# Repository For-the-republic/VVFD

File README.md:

# VVFD
 Variable VFD display driver for any electromagnet based VFD.
 made by Sam Ramsay and Luke Quigley
# PREREQUISTES

## It must have a leakage current
VFDs are funny little things, as even though the have vacumn in the name, most are not a pure vacumn. instead they have a small amount of gas in them. this is only true for larger ( or more delacite ones), and is the main operation which we are measuring to find the anode connections.

## how to tell if you have a leakage current
the best way to tell if it has a leakage current is by the datasheet. if it has **both** a current draw on the segment and grid, you have a leakage. 

the next best way to tell is by the size of the VFD. smaller VFDs tend to be pure vacumns, and dont have a leakage current. if it is a larger (or older) VFD like those found in audio amplifiers, car radios ect, it most likely has a leakage current.

the third and final way to tell is to manually check. if there is a leakage current, **there will be a small current increase when a valid grid/segment combination is found**. this is by far the best way to tell, however can be quite finnicky and so we reccomend the other ways first.

# how this works
 it detects a leakage in current across different pins, and will make an anode connection table accordingly.
  this is still in development so it might take a while to get up and running.

# setup process and PCB information
the PCB is designed to be cascaded for extra modules to fit your VFD size. each module can have 32 pins, and only requires the cascade/vfd driver components. the original board will still need the drivers, but no other ones will.
## setup information
the two values you will need to change  are:
- PINCOUNT
PINCOUNT is the number of shift registers used, starting from the main module and cascading to the right. we need to know this so we can properly push the right bits.

compile this code to your arduino, and have it plugged in to accept serial out. the arduino will print your matrix to the serial out, so its kinda important.

to set the base conditions, the the arduino runs it will go into setup mode for one minute. this gives you time to ajust the variable resistors, and make sure everything is working. **DO NOT CHANGE THE RESISTORS AFTER ONE MINUTE**, or else the ammeters wont have a base value to test off of.

once this mode is done, just leave it. 
## when it has finished
once it has completed making the pinout table, it will cycle through every valid combonation and send a matrix to the serial out of the arduino.

## a note about pinouts
**if in doubt, use the pinout schematic/PCB provided**
- the AC generator pins must be both PWN pins
- the ammeter pins must be analouge
- all other pins should combos should be fine

[video of it working](https://youtu.be/ehEdY2yYjXk)

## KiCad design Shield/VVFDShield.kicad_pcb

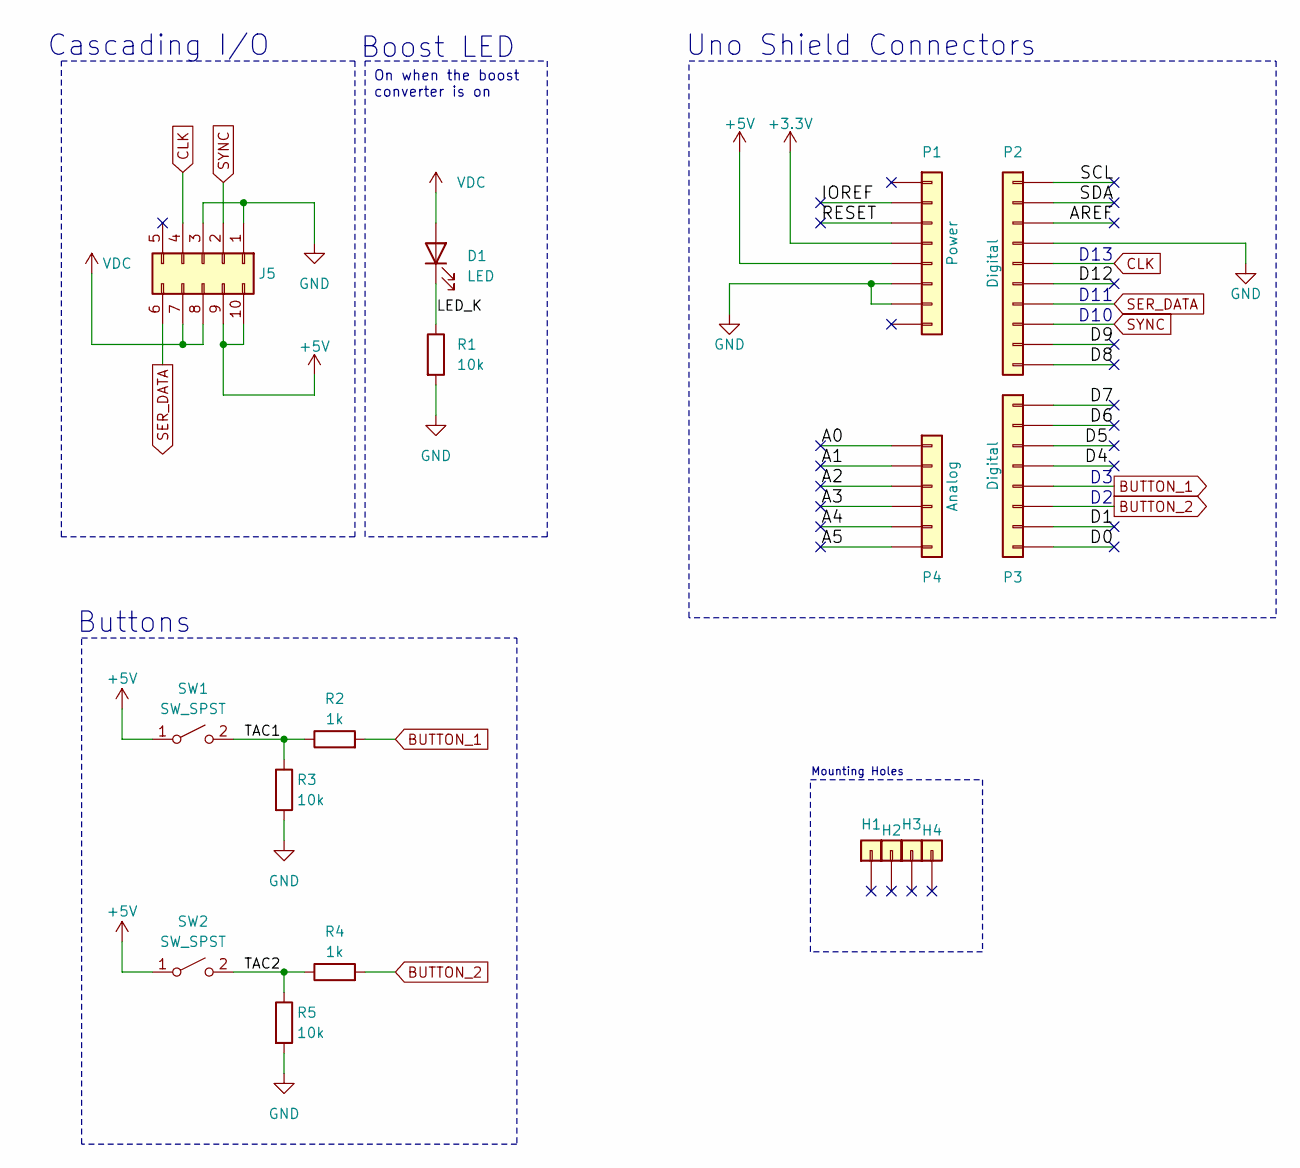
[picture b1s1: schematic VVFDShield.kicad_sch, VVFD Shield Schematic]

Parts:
D1: LED; LED_D5.0mm
H1, H2, H3, H4: CONN_01X01; Mounting_Hole
J5: Conn_02x05_Counter_Clockwise; IDC-Header_2x05_P2.54mm_Vertical; Digikey Part No UC
P1: Power; Socket_Strip_Arduino_1x08
P2: Digital; Socket_Strip_Arduino_1x10
P3: Digital; Socket_Strip_Arduino_1x08
P4: Analog; Socket_Strip_Arduino_1x06
R1, R3, R5: 10k; R_Axial_DIN0207_L6.3mm_D2.5mm_P7.62mm_Horizontal
R2, R4: 1k; R_Axial_DIN0207_L6.3mm_D2.5mm_P7.62mm_Horizontal
SW1, SW2: SW_SPST; SW_PUSH_6mm

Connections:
+3.3V: P1.4
+5V: J5.9, J5.10, P1.5, SW1.1 (A), SW2.1 (A)
/A0: P4.1
/A1: P4.2
/A2: P4.3
/A3: P4.4
/A4: P4.5
/A5: P4.6
/AREF: P2.3
/D0: P3.8
/D1: P3.7
/D4: P3.4
/D5: P3.3
/D6: P3.2
/D7: P3.1
/D8: P2.10
/D9: P2.9
/D12: P2.6
/IOREF: P1.2
/LED_K: D1.1 (K), R1.1
/RESET: P1.3
/SCL: P2.1
/SDA: P2.2
/TAC1: R2.1, R3.1, SW1.2 (B)
/TAC2: R4.1, R5.1, SW2.2 (B)
BUTTON_1: P3.5, R2.2
BUTTON_2: P3.6, R4.2
CLK: J5.4, P2.5
GND: J5.1, J5.3, P1.6, P1.7, P2.4, R1.2, R3.2, R5.2
SER_DATA: J5.6, P2.7
SYNC: J5.2, P2.8
VDC: D1.2 (A), J5.7, J5.8

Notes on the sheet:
Cascading I/O
Uno Shield Connectors
Buttons
Boost LED
D13
Mounting Holes
D10
D11
On when the boost converter is on

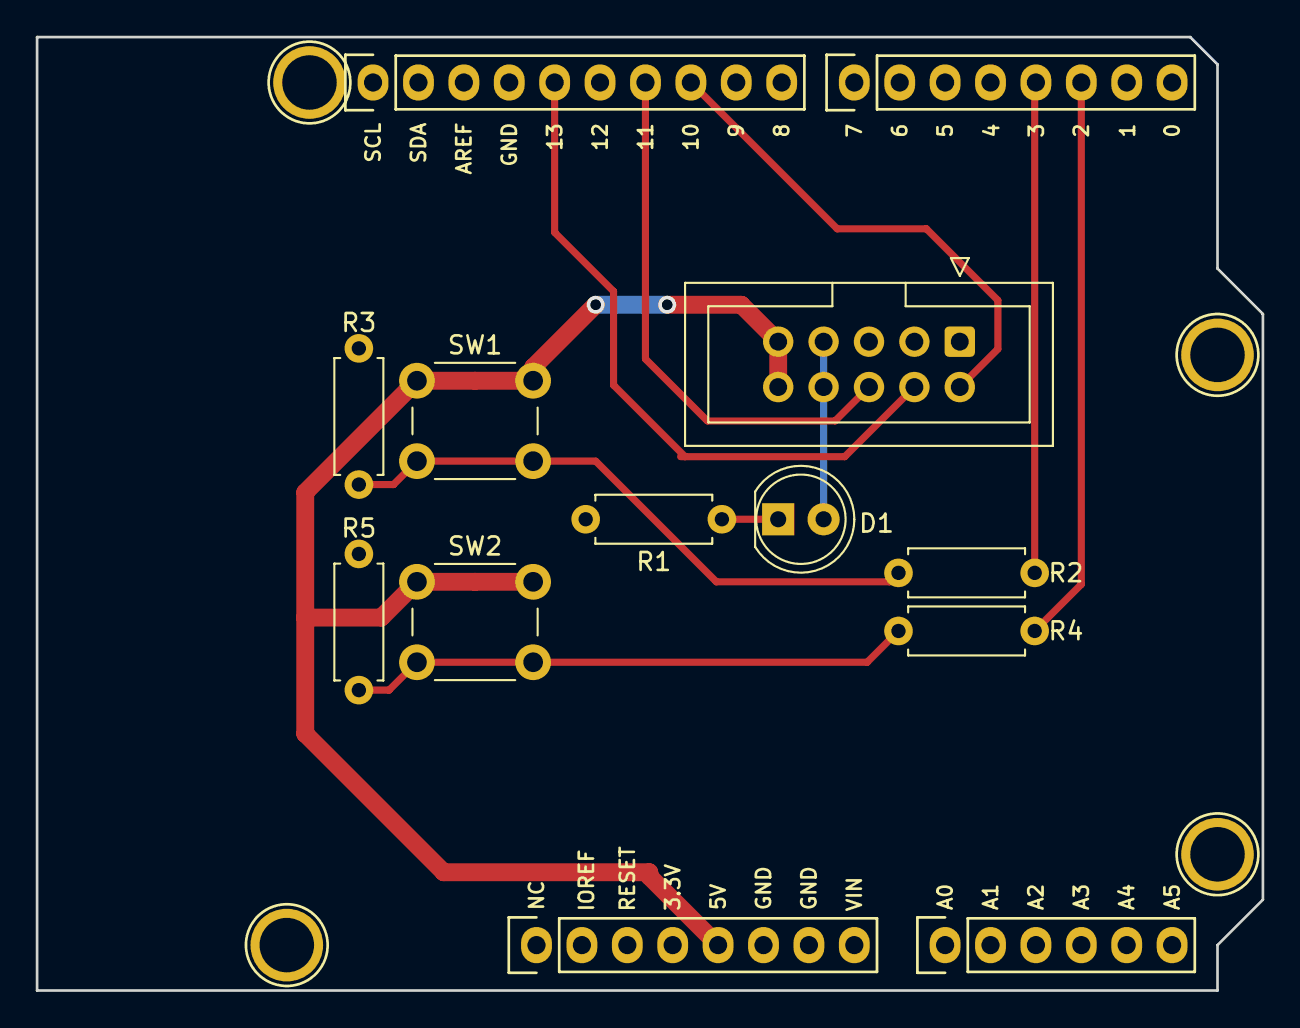
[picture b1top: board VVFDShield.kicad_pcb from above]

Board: 2 copper layers, 68.6 x 53.3 mm, 17 parts (0 on the bottom side), 11 nets.

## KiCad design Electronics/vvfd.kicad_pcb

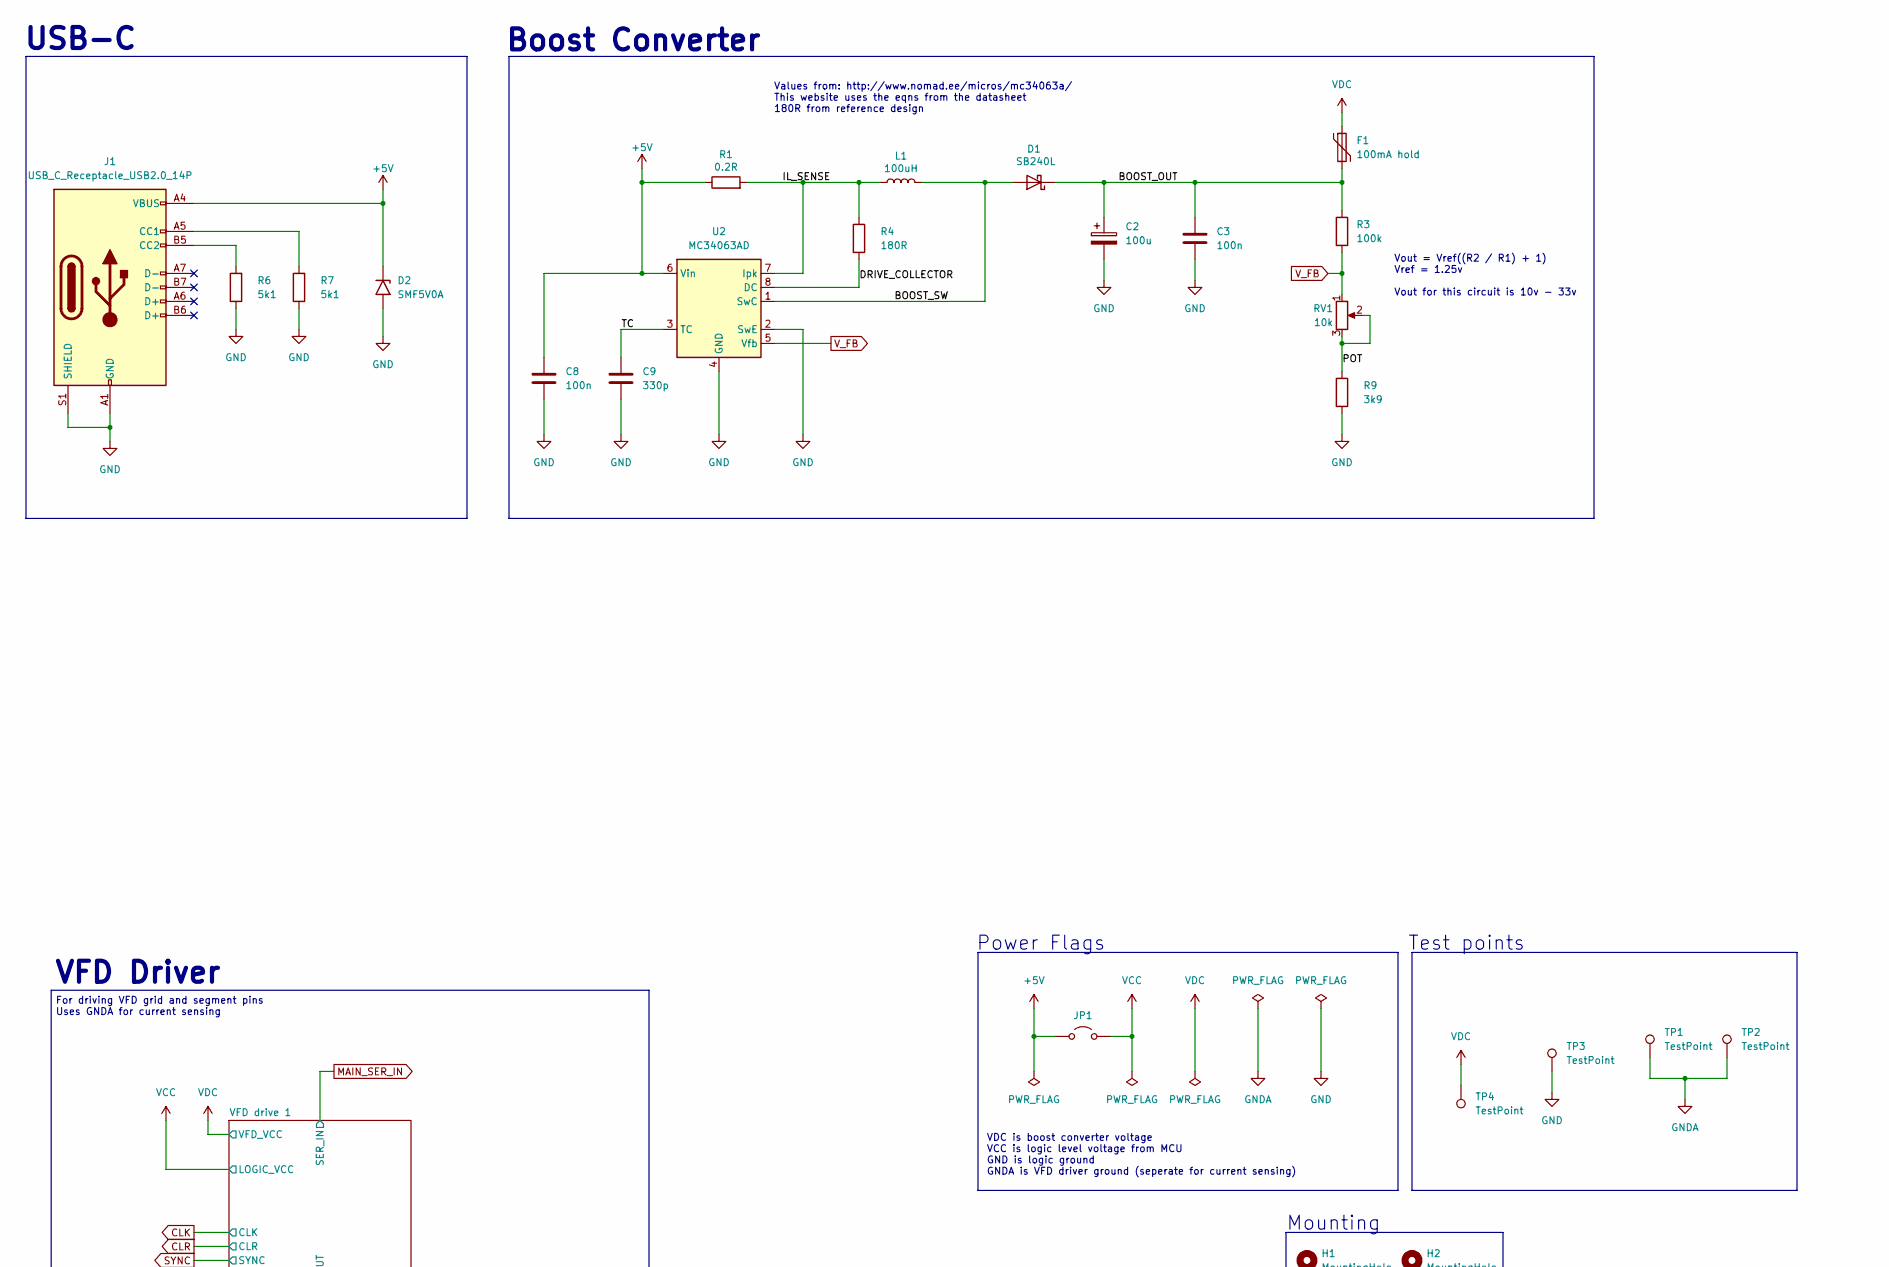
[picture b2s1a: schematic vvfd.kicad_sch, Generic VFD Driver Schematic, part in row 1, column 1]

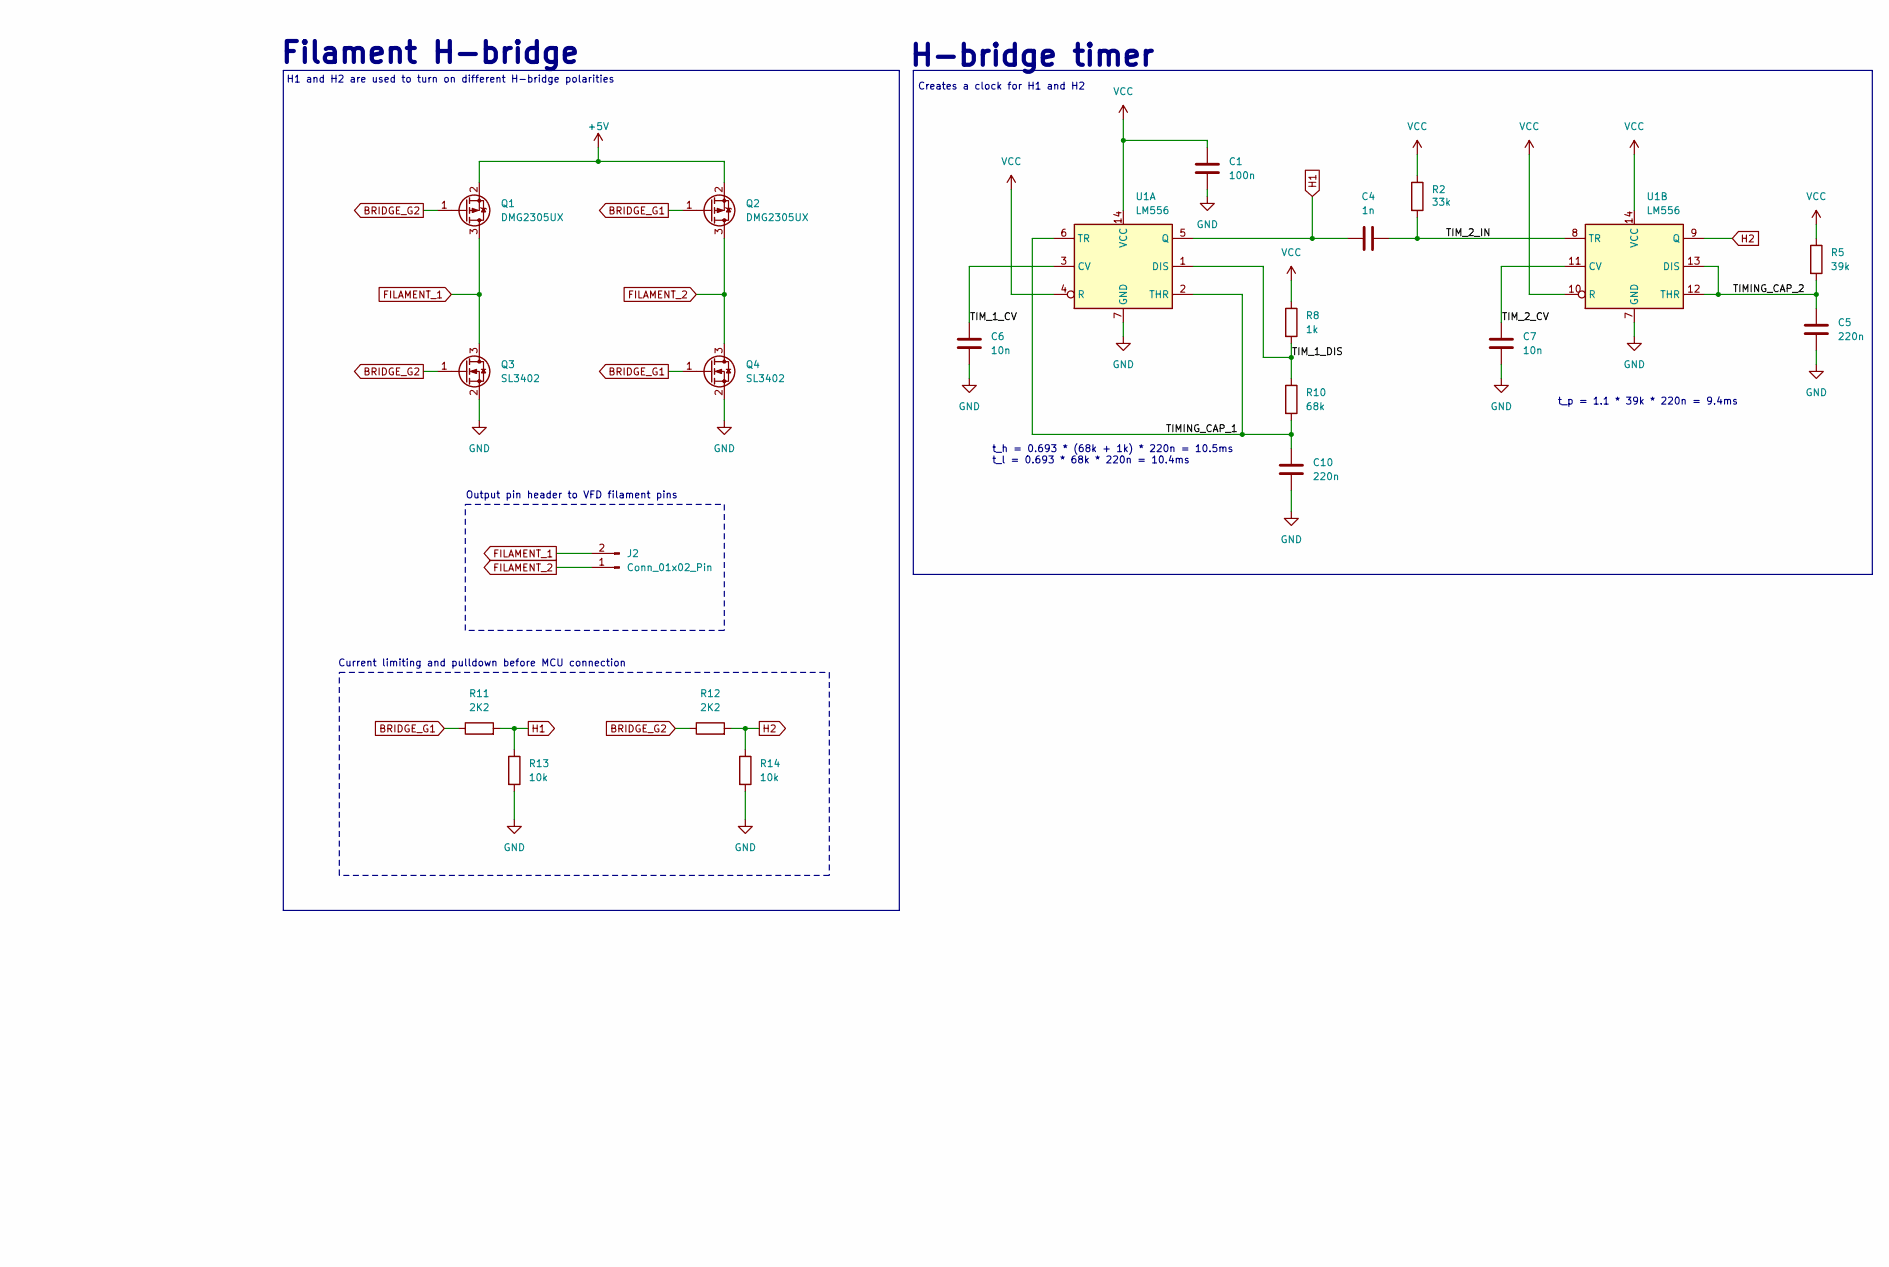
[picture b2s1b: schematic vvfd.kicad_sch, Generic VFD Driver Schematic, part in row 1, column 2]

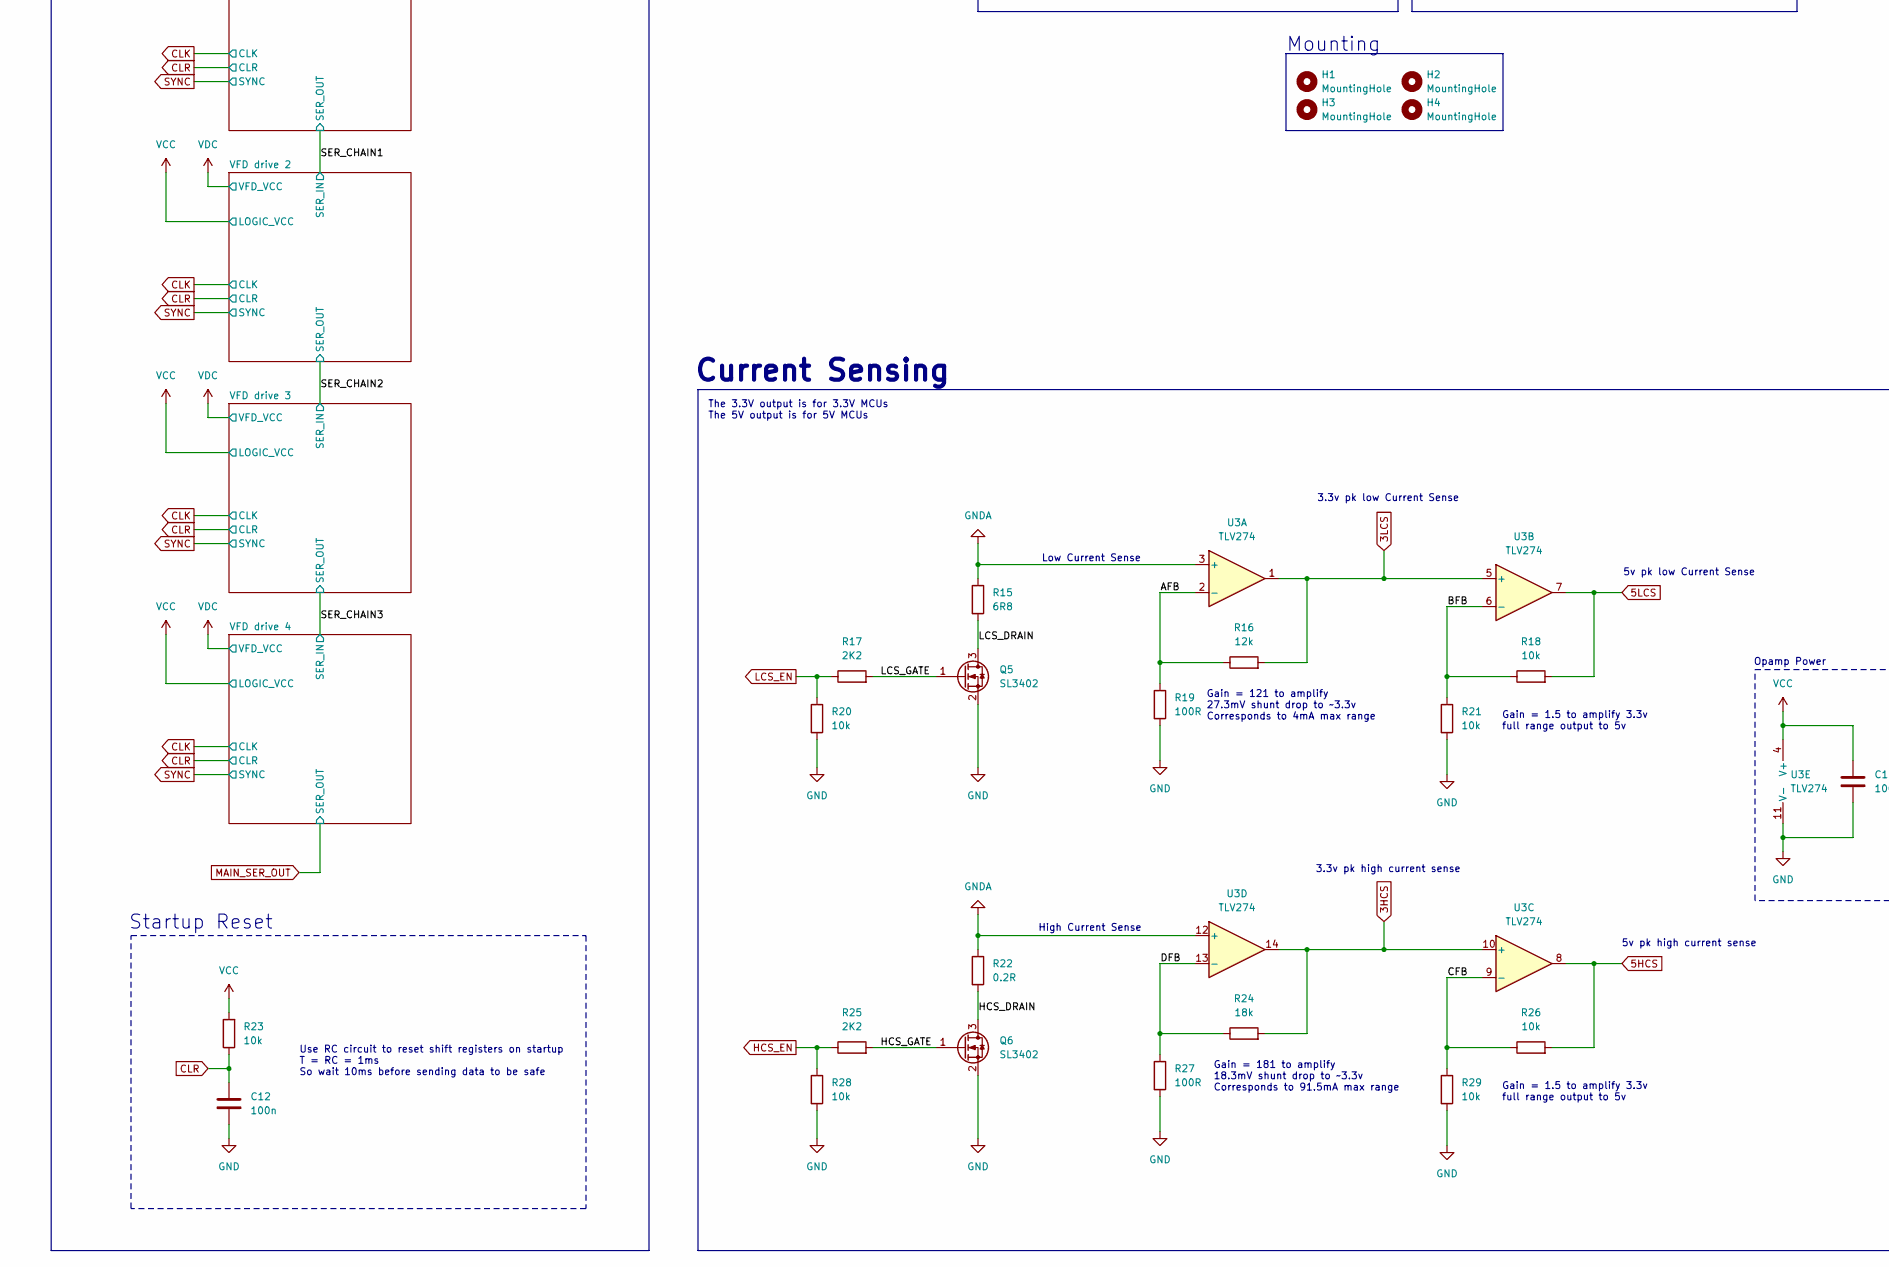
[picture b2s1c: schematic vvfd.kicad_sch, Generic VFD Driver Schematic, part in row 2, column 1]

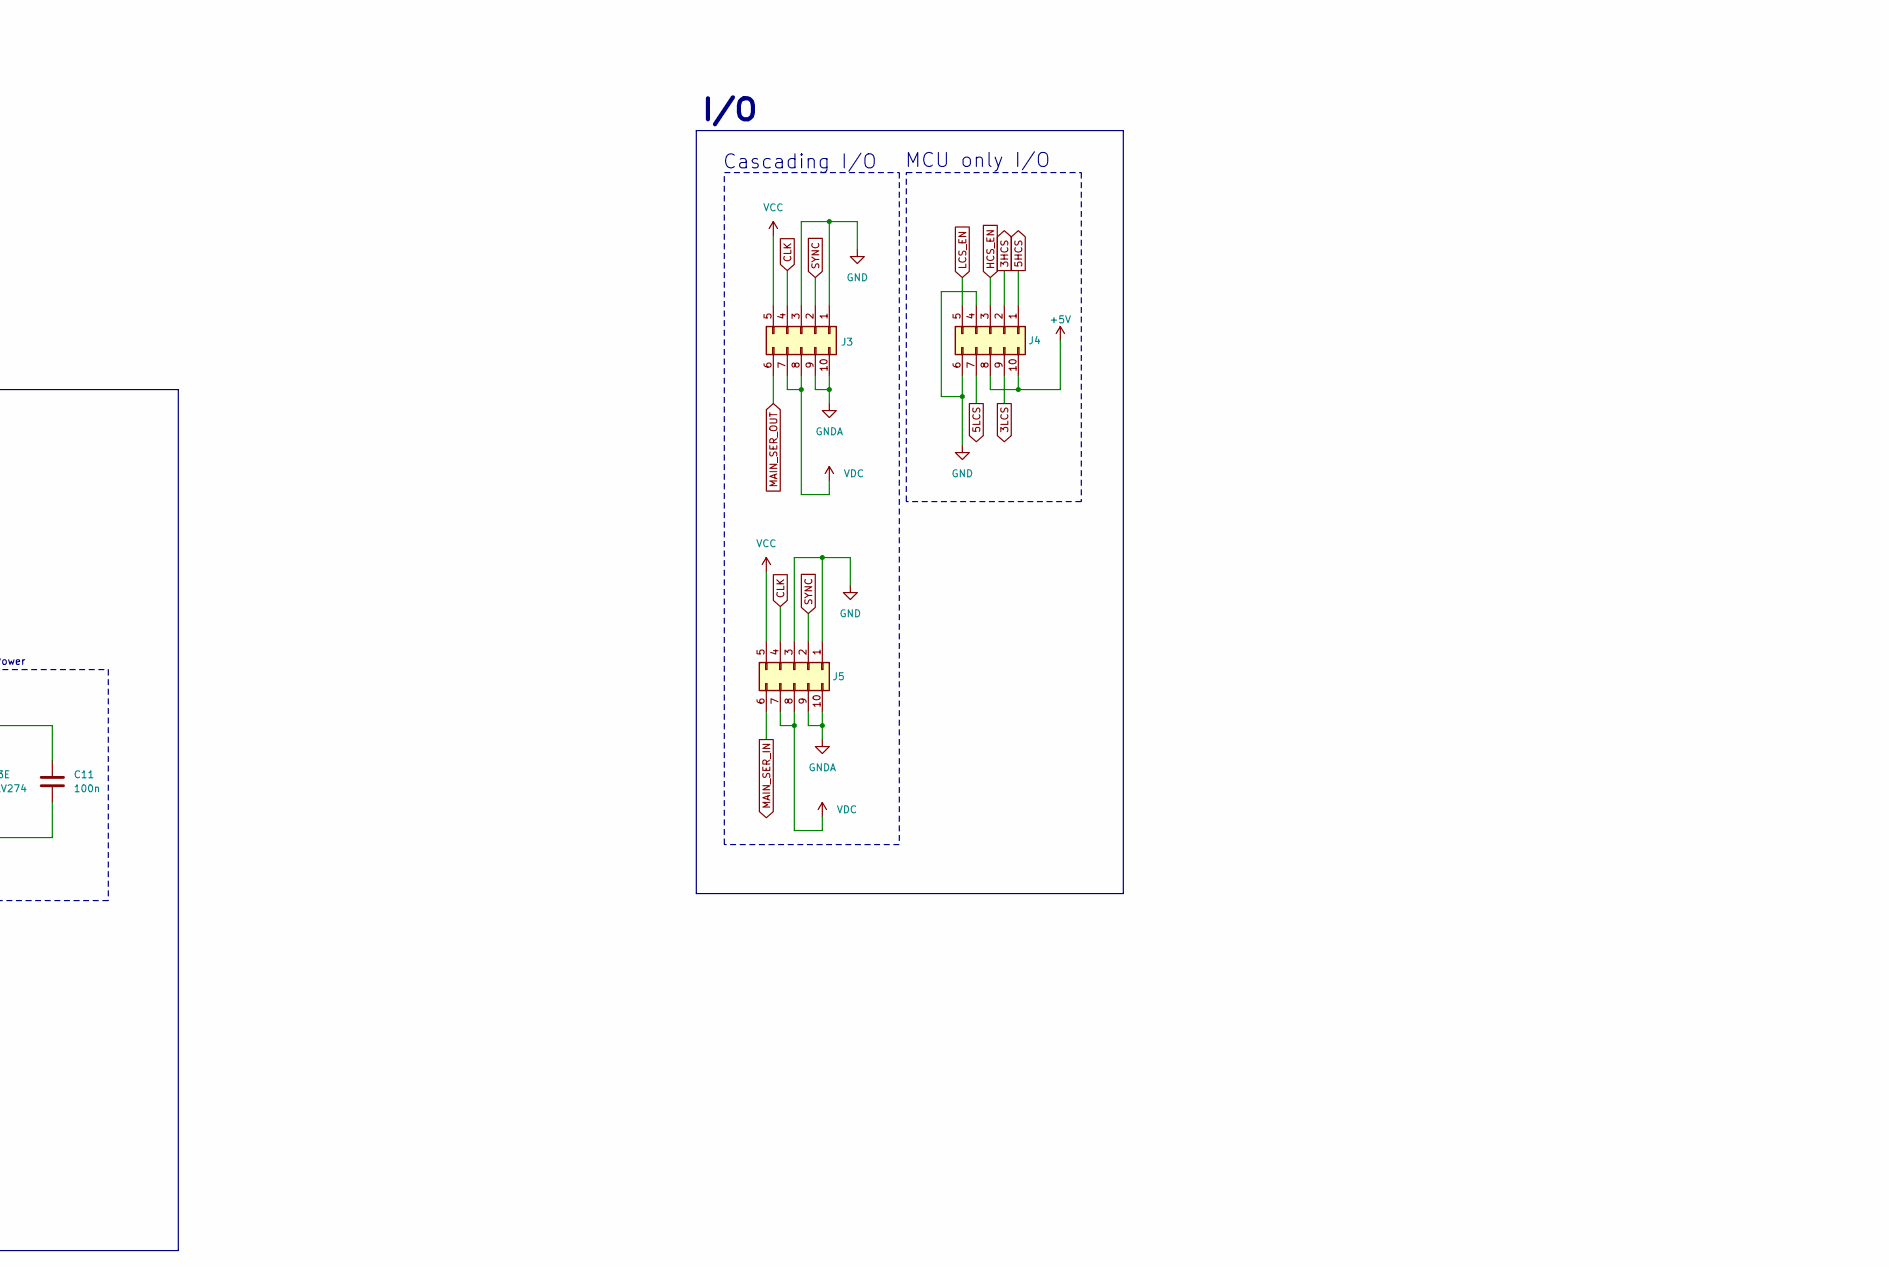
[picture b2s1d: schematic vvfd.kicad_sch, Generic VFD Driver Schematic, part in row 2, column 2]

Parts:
C1, C3, C8, C11, C12: 100n; C_Disc_D5.1mm_W3.2mm_P5.00mm; Digikey Part No UC
C2: 100u; C_Radial_D8.0mm_H11.5mm_P3.50mm; Manufacturer Part No 860080674009; Digikey Part No 732-9051-1-ND
C4: 1n; C_Disc_D5.1mm_W3.2mm_P5.00mm; Digikey Part No UC
C5, C10: 220n; C_Disc_D5.1mm_W3.2mm_P5.00mm; Digikey Part No UC
C6, C7: 10n; C_Disc_D5.1mm_W3.2mm_P5.00mm; Digikey Part No UC
C9: 330p; C_Disc_D5.1mm_W3.2mm_P5.00mm; Digikey Part No UC
D1: SB240L; D_DO-15_P3.81mm_Vertical_KathodeUp; Manufacturer Part No SB240L; Digikey Part No UC
D2: SMF5V0A; D_SMF; Manufacturer Part No SMF5.0A; Digikey Part No 4878-SMF5.0ACT-ND
F1: 100mA hold; Fuse_Littelfuse_395Series; Manufacturer Part No TRF250-120; Digikey Part No UC
H1, H2, H3, H4: MountingHole; MountingHole_3.2mm_M3
J1: USB_C_Receptacle_USB2.0_14P; USB_C_Receptacle_GCT_USB4125-xx-x-0190_6P_TopMnt_Horizontal; Manufacturer Part No UJC-H-G-SMT-P6-TR; Digikey Part No 2223-UJC-H-G-SMT-P6-TRCT-ND
J2: Conn_01x02_Pin; PinHeader_1x02_P2.54mm_Vertical; Digikey Part No UC
J3, J4, J5: Conn_02x05_Counter_Clockwise; IDC-Header_2x05_P2.54mm_Vertical; Digikey Part No UC
JP1: Jumper_2_Open; PinHeader_1x02_P2.54mm_Vertical; Digikey Part No UC
L1: 100uH; SPM7054VT-D; Manufacturer Part No SPM7054VT-101M-D; Digikey Part No 445-180962-1-ND
Q1, Q2: DMG2305UX; SOT-23; Manufacturer Part No DMG2305UX-7; Digikey Part No DMG2305UX-7DICT-ND
Q3, Q4, Q5, Q6: SL3402; SOT-23; Manufacturer Part No SL3402; Digikey Part No 5399-SL3402CT-ND
R1, R22: 0.2R; R_1206_3216Metric_Pad1.30x1.75mm_HandSolder; Manufacturer Part No MFHA1206R2000FC; Digikey Part No 283-MFHA1206R2000FCCT-ND
R2: 33k; R_Axial_DIN0207_L6.3mm_D2.5mm_P2.54mm_Vertical; Digikey Part No UC
R3: 100k; R_Axial_DIN0207_L6.3mm_D2.5mm_P7.62mm_Horizontal; Digikey Part No UC
R4: 180R; R_Axial_DIN0207_L6.3mm_D2.5mm_P2.54mm_Vertical; Digikey Part No UC
R5: 39k; R_Axial_DIN0207_L6.3mm_D2.5mm_P2.54mm_Vertical; Digikey Part No UC
R6, R7: 5k1; R_Axial_DIN0207_L6.3mm_D2.5mm_P2.54mm_Vertical; Digikey Part No UC
R8: 1k; R_Axial_DIN0207_L6.3mm_D2.5mm_P2.54mm_Vertical; Digikey Part No UC
R9: 3k9; R_Axial_DIN0207_L6.3mm_D2.5mm_P2.54mm_Vertical; Digikey Part No UC
R10: 68k; R_Axial_DIN0207_L6.3mm_D2.5mm_P2.54mm_Vertical; Digikey Part No UC
R11, R12: 2K2; R_Axial_DIN0207_L6.3mm_D2.5mm_P7.62mm_Horizontal; Digikey Part No UC
R13, R14, R23: 10k; R_Axial_DIN0207_L6.3mm_D2.5mm_P7.62mm_Horizontal; Digikey Part No UC
R15: 6R8; R_Axial_DIN0207_L6.3mm_D2.5mm_P2.54mm_Vertical; Digikey Part No UC
R16: 12k; R_Axial_DIN0207_L6.3mm_D2.5mm_P2.54mm_Vertical; Digikey Part No UC
R17, R25: 2K2; R_Axial_DIN0207_L6.3mm_D2.5mm_P2.54mm_Vertical; Digikey Part No UC
R18, R20, R21, R26, R28, R29: 10k; R_Axial_DIN0207_L6.3mm_D2.5mm_P2.54mm_Vertical; Digikey Part No UC
R19, R27: 100R; R_Axial_DIN0207_L6.3mm_D2.5mm_P2.54mm_Vertical; Digikey Part No UC
R24: 18k; R_Axial_DIN0207_L6.3mm_D2.5mm_P2.54mm_Vertical; Digikey Part No UC
RV1: 10k; Potentiometer_Bourns_3296W_Vertical; Manufacturer Part No 3296W; Digikey Part No UC
TP1, TP2: TestPoint; TestPoint_Pad_4.0x4.0mm
TP3, TP4: TestPoint; TestPoint_Pad_D2.0mm
U1: LM556; DIP-14_W7.62mm; Manufacturer Part No LM557; Digikey Part No UC
U2: MC34063AD; SOIC-8_3.9x4.9mm_P1.27mm; Manufacturer Part No MC34063S; Digikey Part No 5399-MC34063SCT-ND
U3: TLV274; DIP-14_W7.62mm; Manufacturer Part No TLV274; Digikey Part No UC

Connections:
3HCS: J4.2, R24.2, U3.10 (+), U3.14
3LCS: J4.9, R16.2, U3.1, U3.5 (+)
5HCS: J4.1, R26.2, U3.8
5LCS: J4.7, R18.2, U3.7
+5V: C8.1, D2.1 (A1), J1.A4 (VBUS), J1.A9 (VBUS), J1.B4 (VBUS), J1.B9 (VBUS), J4.8, J4.10, JP1.1 (A), Q1.2 (S), Q2.2 (S), R1.1, U2.6 (Vin)
/AFB: R16.1, R19.1, U3.2 (-)
/BFB: R18.1, R21.1, U3.6 (-)
/BOOST_OUT: C2.1, C3.1, D1.1 (K), F1.2, R3.1
/BOOST_SW: D1.2 (A), L1.2, U2.1 (SwC)
/CFB: R26.1, R29.1, U3.9 (-)
/DFB: R24.1, R27.1, U3.13 (-)
/DRIVE_COLLECTOR: R4.2, U2.8 (DC)
/HCS_DRAIN: Q6.3 (D), R22.2
/HCS_GATE: Q6.1 (G), R25.2
/IL_SENSE: L1.1, R1.2, R4.1, U2.7 (Ipk)
/LCS_DRAIN: Q5.3 (D), R15.2
/LCS_GATE: Q5.1 (G), R17.2
/POT: R9.1, RV1.2, RV1.3
/TC: C9.1, U2.3 (TC)
/TIMING_CAP_1: C10.1, R10.2, U1.2 (THR), U1.6 (TR)
/TIMING_CAP_2: C5.1, R5.2, U1.12 (THR), U1.13 (DIS)
/TIM_1_CV: C6.1, U1.3 (CV)
/TIM_1_DIS: R8.2, R10.1, U1.1 (DIS)
/TIM_2_CV: C7.1, U1.11 (CV)
/TIM_2_IN: C4.2, R2.2, U1.8 (TR)
BRIDGE_G1: Q2.1 (G), Q4.1 (G), R11.1
BRIDGE_G2: Q1.1 (G), Q3.1 (G), R12.1
CLK: J3.4, J5.4; also elsewhere on the board
CLR: C12.1, R23.1; also elsewhere on the board
FILAMENT_1: J2.2, Q1.3 (D), Q3.3 (D)
FILAMENT_2: J2.1, Q2.3 (D), Q4.3 (D)
GND: C1.2, C2.2, C3.2, C5.2, C6.2, C7.2, C8.2, C9.2, C10.2, C11.2, C12.2, D2.2 (A2), J1.A1 (GND), J1.A12 (GND), J1.B1 (GND), J1.B12 (GND), J1.S1 (SHIELD), J3.1, J3.3, J4.4, J4.6, J5.1, J5.3, Q3.2 (S), Q4.2 (S), Q5.2 (S), Q6.2 (S), R6.1, R7.1, R9.2, R13.2, R14.2, R19.2, R20.2, R21.2, R27.2, R28.2, R29.2, TP3.1, U1.7 (GND), U2.2 (SwE), U2.4 (GND), U3.11 (V-); also elsewhere on the board
GNDA: J3.9, J3.10, J5.9, J5.10, R15.1, R22.1, TP1.1, TP2.1, U3.3 (+), U3.12 (+); also elsewhere on the board
H1: C4.1, R11.2, R13.1, U1.5 (Q)
H2: R12.2, R14.1, U1.9 (Q)
HCS_EN: J4.3, R25.1, R28.1
LCS_EN: J4.5, R17.1, R20.1
MAIN_SER_IN: J5.6; also elsewhere on the board
MAIN_SER_OUT: J3.6; also elsewhere on the board
unnamed: J1.A5 (CC1), R7.2
unnamed: J1.B5 (CC2), R6.2
SYNC: J3.2, J5.2; also elsewhere on the board
VCC: C1.1, C11.1, J3.5, J5.5, JP1.2 (B), R2.1, R5.1, R8.1, R23.2, U1.4 (R), U1.10 (R), U1.14 (VCC), U3.4 (V+); also elsewhere on the board
VDC: F1.1, J3.7, J3.8, J5.7, J5.8, TP4.1; also elsewhere on the board
V_FB: R3.2, RV1.1, U2.5 (Vfb)

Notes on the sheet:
3.3v pk low Current Sense
5v pk high current sense
Values from: http://www.nomad.ee/micros/mc34063a/ This website uses the eqns from the datasheet 180R from reference design
Vout = Vref((R2 / R1) + 1) Vref = 1.25v Vout for this circuit is 10v - 33v
Startup Reset
MCU only I/O
VDC is boost converter voltage VCC is logic level voltage from MCU GND is logic ground GNDA is VFD driver ground (seperate for current sensing)
The 3.3V output is for 3.3V MCUs The 5V output is for 5V MCUs
Power Flags
Gain = 181 to amplify 18.3mV shunt drop to ~3.3v Corresponds to 91.5mA max range
5v pk low Current Sense
3.3v pk high current sense
I/O
Filament H-bridge
t_h = 0.693 * (68k + 1k) * 220n = 10.5ms t_l = 0.693 * 68k * 220n = 10.4ms
High Current Sense
Mounting
Opamp Power
H-bridge timer
Low Current Sense
t_p = 1.1 * 39k * 220n = 9.4ms
For driving VFD grid and segment pins Uses GNDA for current sensing
Creates a clock for H1 and H2
VFD Driver
Cascading I/O
Current Sensing
Use RC circuit to reset shift registers on startup T = RC = 1ms So wait 10ms before sending data to be safe
Gain = 1.5 to amplify 3.3v full range output to 5v
Gain = 121 to amplify 27.3mV shunt drop to ~3.3v Corresponds to 4mA max range
USB-C
Current limiting and pulldown before MCU connection
Test points
H1 and H2 are used to turn on different H-bridge polarities
Output pin header to VFD filament pins
Boost Converter

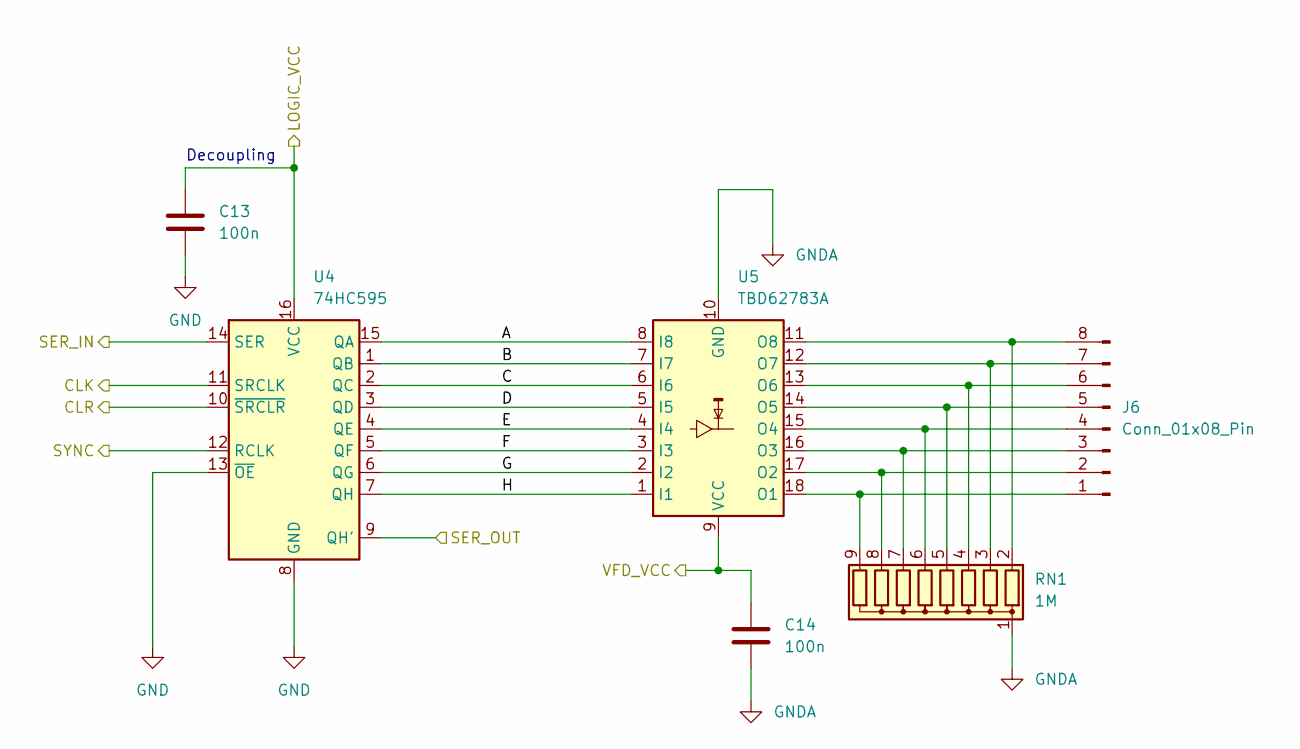
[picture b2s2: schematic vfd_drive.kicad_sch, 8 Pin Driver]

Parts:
C13, C14: 100n; C_Disc_D5.1mm_W3.2mm_P5.00mm; Digikey Part No UC
J6: Conn_01x08_Pin; PinHeader_1x08_P2.54mm_Vertical; Digikey Part No UC
RN1: 1M; R_Array_SIP9; Manufacturer Part No 4609X-101-474LF; Digikey Part No 4609X-101-474LF-ND
U4: 74HC595; DIP-16_W7.62mm; Manufacturer Part No 74HC595; Digikey Part No UC
U5: TBD62783A; SOP-18_7x12.5mm_P1.27mm; Manufacturer Part No TBD62783AFG,EL; Digikey Part No TBD62783AFGELCT-ND

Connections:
/SER_CHAIN1: U4.9 (QH'); also elsewhere on the board
/VFD drive 1/A: U4.15 (QA), U5.8 (I8)
/VFD drive 1/B: U4.1 (QB), U5.7 (I7)
/VFD drive 1/C: U4.2 (QC), U5.6 (I6)
/VFD drive 1/D: U4.3 (QD), U5.5 (I5)
/VFD drive 1/E: U4.4 (QE), U5.4 (I4)
/VFD drive 1/F: U4.5 (QF), U5.3 (I3)
/VFD drive 1/G: U4.6 (QG), U5.2 (I2)
/VFD drive 1/H: U4.7 (QH), U5.1 (I1)
CLK: U4.11 (SRCLK); also elsewhere on the board
CLR: U4.10 (~SRCLR); also elsewhere on the board
GND: C13.2, U4.8 (GND), U4.13 (~OE); also elsewhere on the board
GNDA: C14.2, RN1.1 (common), U5.10 (GND); also elsewhere on the board
MAIN_SER_IN: U4.14 (SER); also elsewhere on the board
unnamed: J6.1, RN1.9 (R8), U5.18 (O1)
unnamed: J6.2, RN1.8 (R7), U5.17 (O2)
unnamed: J6.3, RN1.7 (R6), U5.16 (O3)
unnamed: J6.4, RN1.6 (R5), U5.15 (O4)
unnamed: J6.5, RN1.5 (R4), U5.14 (O5)
unnamed: J6.6, RN1.4 (R3), U5.13 (O6)
unnamed: J6.7, RN1.3 (R2), U5.12 (O7)
unnamed: J6.8, RN1.2 (R1), U5.11 (O8)
SYNC: U4.12 (RCLK); also elsewhere on the board
VCC: C13.1, U4.16 (VCC); also elsewhere on the board
VDC: C14.1, U5.9 (VCC); also elsewhere on the board

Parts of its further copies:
C15, C16, C17, C18, C19, C20: 100n; C_Disc_D5.1mm_W3.2mm_P5.00mm; Digikey Part No UC
J7, J8, J9: Conn_01x08_Pin; PinHeader_1x08_P2.54mm_Vertical; Digikey Part No UC
RN2, RN3, RN4: 1M; R_Array_SIP9; Manufacturer Part No 4609X-101-474LF; Digikey Part No 4609X-101-474LF-ND
U6, U8, U10: 74HC595; DIP-16_W7.62mm; Manufacturer Part No 74HC595; Digikey Part No UC
U7, U9, U11: TBD62783A; SOP-18_7x12.5mm_P1.27mm; Manufacturer Part No TBD62783AFG,EL; Digikey Part No TBD62783AFGELCT-ND

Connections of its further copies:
/SER_CHAIN1: U6.14 (SER); also elsewhere on the board
/SER_CHAIN2: U6.9 (QH'), U8.14 (SER)
/SER_CHAIN3: U8.9 (QH'), U10.14 (SER)
/VFD drive 2/A: U6.15 (QA), U7.8 (I8)
/VFD drive 2/B: U6.1 (QB), U7.7 (I7)
/VFD drive 2/C: U6.2 (QC), U7.6 (I6)
/VFD drive 2/D: U6.3 (QD), U7.5 (I5)
/VFD drive 2/E: U6.4 (QE), U7.4 (I4)
/VFD drive 2/F: U6.5 (QF), U7.3 (I3)
/VFD drive 2/G: U6.6 (QG), U7.2 (I2)
/VFD drive 2/H: U6.7 (QH), U7.1 (I1)
/VFD drive 3/A: U8.15 (QA), U9.8 (I8)
/VFD drive 3/B: U8.1 (QB), U9.7 (I7)
/VFD drive 3/C: U8.2 (QC), U9.6 (I6)
/VFD drive 3/D: U8.3 (QD), U9.5 (I5)
/VFD drive 3/E: U8.4 (QE), U9.4 (I4)
/VFD drive 3/F: U8.5 (QF), U9.3 (I3)
/VFD drive 3/G: U8.6 (QG), U9.2 (I2)
/VFD drive 3/H: U8.7 (QH), U9.1 (I1)
/VFD drive 4/A: U10.15 (QA), U11.8 (I8)
/VFD drive 4/B: U10.1 (QB), U11.7 (I7)
/VFD drive 4/C: U10.2 (QC), U11.6 (I6)
/VFD drive 4/D: U10.3 (QD), U11.5 (I5)
/VFD drive 4/E: U10.4 (QE), U11.4 (I4)
/VFD drive 4/F: U10.5 (QF), U11.3 (I3)
/VFD drive 4/G: U10.6 (QG), U11.2 (I2)
/VFD drive 4/H: U10.7 (QH), U11.1 (I1)
CLK: U6.11 (SRCLK), U8.11 (SRCLK), U10.11 (SRCLK); also elsewhere on the board
CLR: U6.10 (~SRCLR), U8.10 (~SRCLR), U10.10 (~SRCLR); also elsewhere on the board
GND: C15.2, C17.2, C19.2, U6.8 (GND), U6.13 (~OE), U8.8 (GND), U8.13 (~OE), U10.8 (GND), U10.13 (~OE); also elsewhere on the board
GNDA: C16.2, C18.2, C20.2, RN2.1 (common), RN3.1 (common), RN4.1 (common), U7.10 (GND), U9.10 (GND), U11.10 (GND); also elsewhere on the board
MAIN_SER_OUT: U10.9 (QH'); also elsewhere on the board
unnamed: J7.1, RN2.9 (R8), U7.18 (O1)
unnamed: J7.2, RN2.8 (R7), U7.17 (O2)
unnamed: J7.3, RN2.7 (R6), U7.16 (O3)
unnamed: J7.4, RN2.6 (R5), U7.15 (O4)
unnamed: J7.5, RN2.5 (R4), U7.14 (O5)
unnamed: J7.6, RN2.4 (R3), U7.13 (O6)
unnamed: J7.7, RN2.3 (R2), U7.12 (O7)
unnamed: J7.8, RN2.2 (R1), U7.11 (O8)
unnamed: J8.1, RN3.9 (R8), U9.18 (O1)
unnamed: J8.2, RN3.8 (R7), U9.17 (O2)
unnamed: J8.3, RN3.7 (R6), U9.16 (O3)
unnamed: J8.4, RN3.6 (R5), U9.15 (O4)
unnamed: J8.5, RN3.5 (R4), U9.14 (O5)
unnamed: J8.6, RN3.4 (R3), U9.13 (O6)
unnamed: J8.7, RN3.3 (R2), U9.12 (O7)
unnamed: J8.8, RN3.2 (R1), U9.11 (O8)
unnamed: J9.1, RN4.9 (R8), U11.18 (O1)
unnamed: J9.2, RN4.8 (R7), U11.17 (O2)
unnamed: J9.3, RN4.7 (R6), U11.16 (O3)
unnamed: J9.4, RN4.6 (R5), U11.15 (O4)
unnamed: J9.5, RN4.5 (R4), U11.14 (O5)
unnamed: J9.6, RN4.4 (R3), U11.13 (O6)
unnamed: J9.7, RN4.3 (R2), U11.12 (O7)
unnamed: J9.8, RN4.2 (R1), U11.11 (O8)
SYNC: U6.12 (RCLK), U8.12 (RCLK), U10.12 (RCLK); also elsewhere on the board
VCC: C15.1, C17.1, C19.1, U6.16 (VCC), U8.16 (VCC), U10.16 (VCC); also elsewhere on the board
VDC: C16.1, C18.1, C20.1, U7.9 (VCC), U9.9 (VCC), U11.9 (VCC); also elsewhere on the board

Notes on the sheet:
Decoupling
